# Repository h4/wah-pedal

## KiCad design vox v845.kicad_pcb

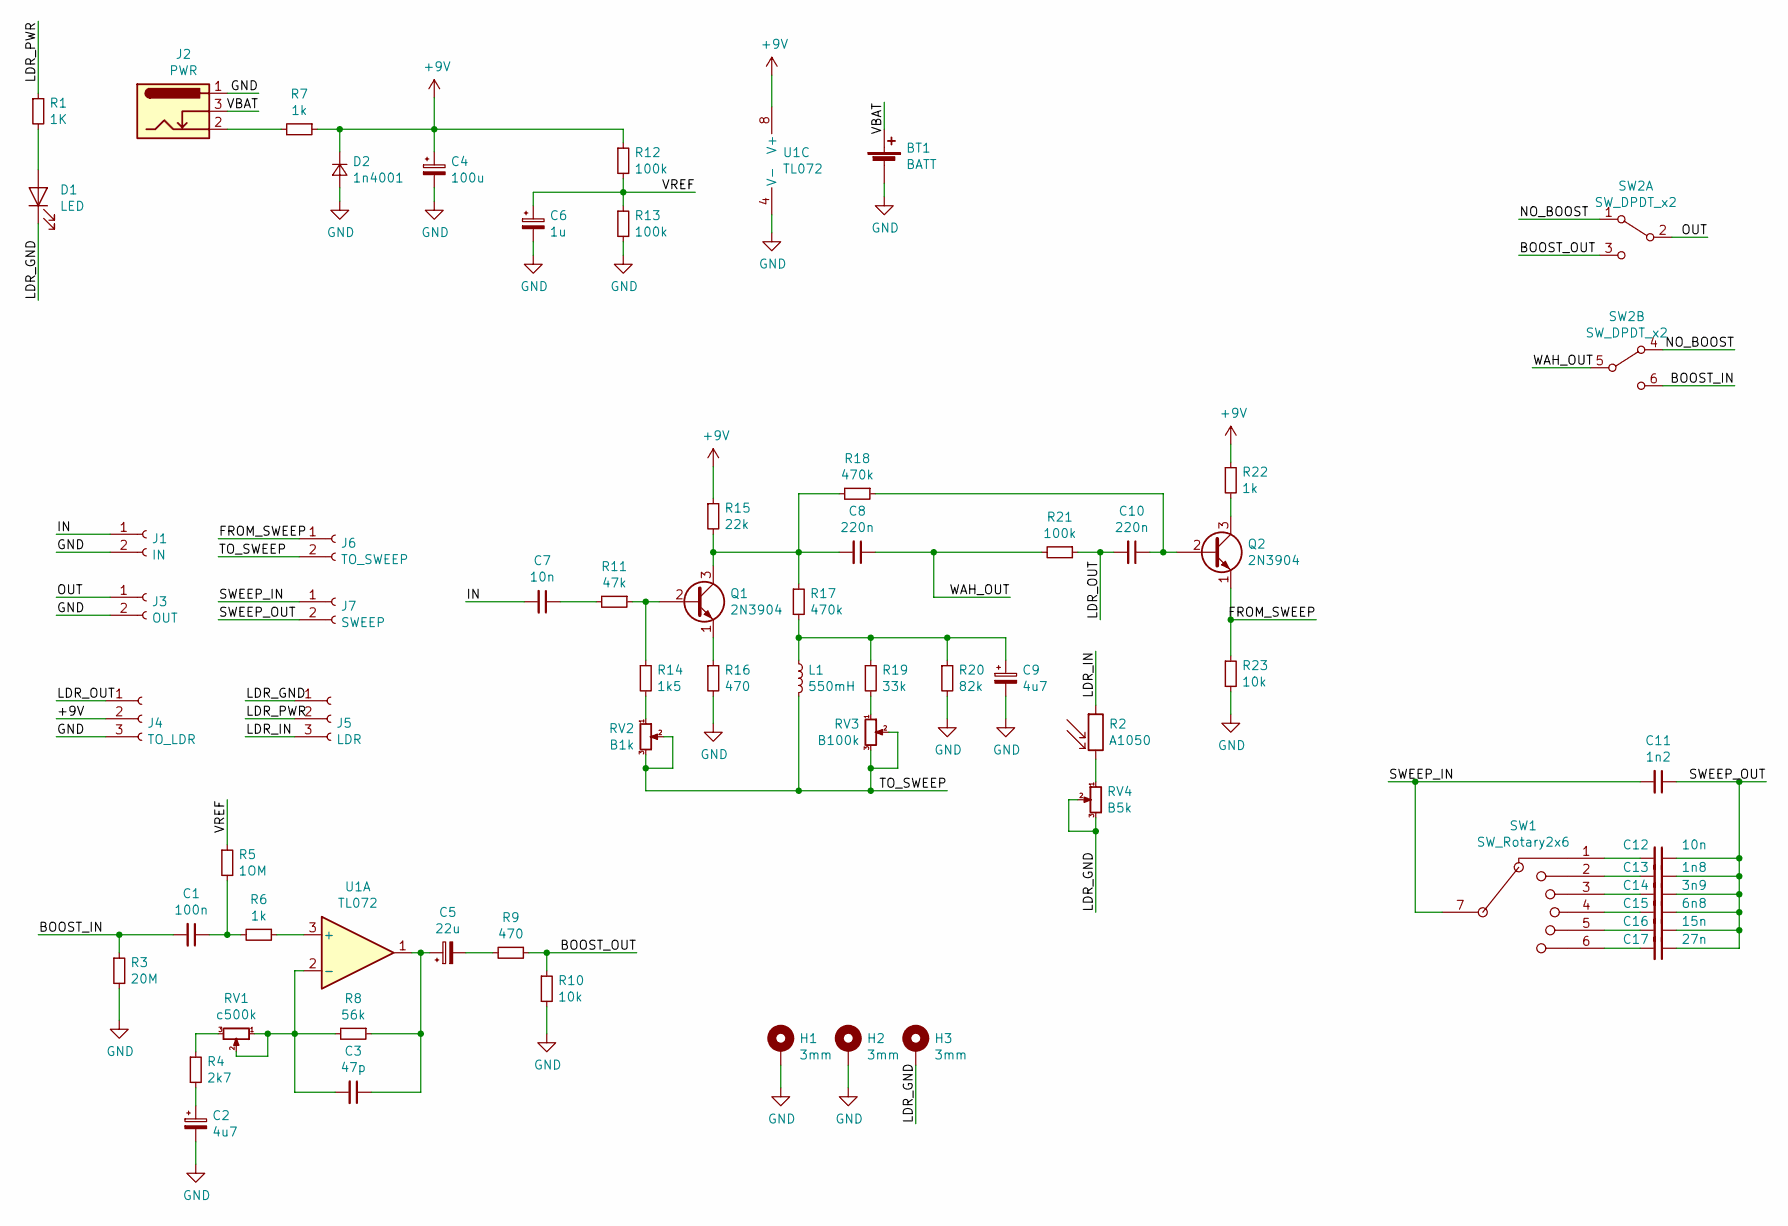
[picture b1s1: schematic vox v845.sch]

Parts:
BT1: BATT; JST_XH_B2B-XH-A_1x02_P2.50mm_Vertical
C1: 100n; C_Rect_L7.0mm_W3.5mm_P5.00mm
C2, C9: 4u7; CP_Radial_D5.0mm_P2.50mm
C3: 47p; C_Disc_D4.3mm_W1.9mm_P5.00mm
C4: 100u; CP_Radial_D8.0mm_P3.80mm
C5: 22u; CP_Radial_D5.0mm_P2.50mm
C6: 1u; CP_Radial_D5.0mm_P2.50mm
C7, C12: 10n; C_Rect_L7.0mm_W3.5mm_P5.00mm
C8, C10: 220n; C_Rect_L7.0mm_W3.5mm_P5.00mm
C11: 1n2; C_Rect_L7.0mm_W3.5mm_P5.00mm
C13: 1n8; C_Rect_L7.0mm_W3.5mm_P5.00mm
C14: 3n9; C_Rect_L7.0mm_W3.5mm_P5.00mm
C15: 6n8; C_Rect_L7.0mm_W3.5mm_P5.00mm
C16: 15n; C_Rect_L7.0mm_W3.5mm_P5.00mm
C17: 27n; C_Rect_L7.0mm_W3.5mm_P5.00mm
D1: LED; LED_D5.0mm_Horizontal_O1.27mm_Z3.0mm
D2: 1n4001; D_DO-15_P12.70mm_Horizontal
H1, H2, H3: 3mm; MountingHole_3.2mm_M3_Pad
J1: IN; JST_XH_B2B-XH-A_1x02_P2.50mm_Vertical
J2: PWR; JST_XH_B3B-XH-A_1x03_P2.50mm_Vertical
J3: OUT; JST_XH_B2B-XH-A_1x02_P2.50mm_Vertical
J4: TO_LDR; JST_XH_B3B-XH-A_1x03_P2.50mm_Vertical
J5: LDR; JST_XH_B3B-XH-A_1x03_P2.50mm_Vertical
J6: TO_SWEEP; JST_XH_B2B-XH-A_1x02_P2.50mm_Vertical
J7: SWEEP; JST_XH_B2B-XH-A_1x02_P2.50mm_Vertical
L1: 550mH; Inductor_VOX_L1A
Q1, Q2: 2N3904; TO-92_Inline_Wide
R1: 1K; R_Axial_DIN0204_L3.6mm_D1.6mm_P7.62mm_Horizontal
R2: A1050; R_LDR_D6.4mm_P3.4mm_Vertical
R3: 20M; R_Axial_DIN0411_L9.9mm_D3.6mm_P15.24mm_Horizontal
R4: 2k7; R_Axial_DIN0411_L9.9mm_D3.6mm_P15.24mm_Horizontal
R5: 1OM; R_Axial_DIN0411_L9.9mm_D3.6mm_P15.24mm_Horizontal
R6, R7, R22: 1k; R_Axial_DIN0411_L9.9mm_D3.6mm_P15.24mm_Horizontal
R8: 56k; R_Axial_DIN0411_L9.9mm_D3.6mm_P15.24mm_Horizontal
R9, R16: 470; R_Axial_DIN0411_L9.9mm_D3.6mm_P15.24mm_Horizontal
R10, R23: 10k; R_Axial_DIN0411_L9.9mm_D3.6mm_P15.24mm_Horizontal
R11: 47k; R_Axial_DIN0411_L9.9mm_D3.6mm_P15.24mm_Horizontal
R12, R13, R21: 100k; R_Axial_DIN0411_L9.9mm_D3.6mm_P15.24mm_Horizontal
R14: 1k5; R_Axial_DIN0411_L9.9mm_D3.6mm_P15.24mm_Horizontal
R15: 22k; R_Axial_DIN0411_L9.9mm_D3.6mm_P15.24mm_Horizontal
R17, R18: 470k; R_Axial_DIN0411_L9.9mm_D3.6mm_P15.24mm_Horizontal
R19: 33k; R_Axial_DIN0411_L9.9mm_D3.6mm_P15.24mm_Horizontal
R20: 82k; R_Axial_DIN0411_L9.9mm_D3.6mm_P15.24mm_Horizontal
RV1: c500k; JST_XH_B3B-XH-A_1x03_P2.50mm_Vertical
RV2: B1k; JST_XH_B3B-XH-A_1x03_P2.50mm_Vertical
RV3: B100k; JST_XH_B3B-XH-A_1x03_P2.50mm_Vertical
RV4: B5k; JST_XH_B3B-XH-A_1x03_P2.50mm_Vertical
SW1: SW_Rotary2x6; JST_XH_B7B-XH-A_1x07_P2.50mm_Vertical
SW2: SW_DPDT_x2; SW_PUSH_DPDT_Horizontal
U1: TL072; DIP-8_W7.62mm_Socket_LongPads

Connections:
+9V: C4.1, D2.1 (K), J4.2, R7.1, R12.1, R15.1, R22.1, U1.8 (V+)
/BOOST_IN: C1.2, R3.1, SW2.6 (C)
/BOOST_OUT: R9.1, R10.1, SW2.3 (C)
/FROM_SWEEP: J6.1, Q2.1 (E), R23.1
/IN: C7.2, J1.1
/LDR_GND: D1.1 (K), H3.1, J5.1, RV4.2, RV4.3
/LDR_IN: J5.3, R2.1
/LDR_OUT: C10.2, J4.1, R21.1
/LDR_PWR: J5.2, R1.1
/NO_BOOST: SW2.1 (A), SW2.4 (A)
/OUT: J3.1, SW2.2 (B)
/SWEEP_IN: C11.2, J7.1, SW1.7
/SWEEP_OUT: C11.1, C12.1, C13.1, C14.1, C15.1, C16.1, C17.1, J7.2
/TO_SWEEP: J6.2, L1.2, RV2.2, RV2.3, RV3.2, RV3.3
/VBAT: BT1.1 (+), J2.3
/VREF: C6.1, R5.1, R12.2, R13.1
/WAH_OUT: C8.1, R21.2, SW2.5 (B)
GND: BT1.2 (-), C2.2, C4.2, C6.2, C9.2, D2.2 (A), H1.1, H2.1, J1.2, J2.1, J3.2, J4.3, R3.2, R10.2, R13.2, R16.2, R20.2, R23.2, U1.4 (V-)
unnamed: C1.1, R5.2, R6.2
unnamed: C2.1, R4.2
unnamed: C3.1, C5.1, R8.1, U1.1
unnamed: C3.2, R8.2, RV1.1, RV1.2, U1.2 (-)
unnamed: C5.2, R9.2
unnamed: C7.1, R11.2
unnamed: C8.2, Q1.3 (C), R15.2, R17.1, R18.2
unnamed: C9.1, L1.1, R17.2, R19.1, R20.1
unnamed: C10.1, Q2.2 (B), R18.1
unnamed: C12.2, SW1.1
unnamed: C13.2, SW1.2
unnamed: C14.2, SW1.3
unnamed: C15.2, SW1.4
unnamed: C16.2, SW1.5
unnamed: C17.2, SW1.6
unnamed: D1.2 (A), R1.2
unnamed: J2.2, R7.2
unnamed: Q1.1 (E), R16.1
unnamed: Q1.2 (B), R11.1, R14.1
unnamed: Q2.3 (C), R22.2
unnamed: R2.2, RV4.1
unnamed: R4.1, RV1.3
unnamed: R6.1, U1.3 (+)
unnamed: R14.2, RV2.1
unnamed: R19.2, RV3.1

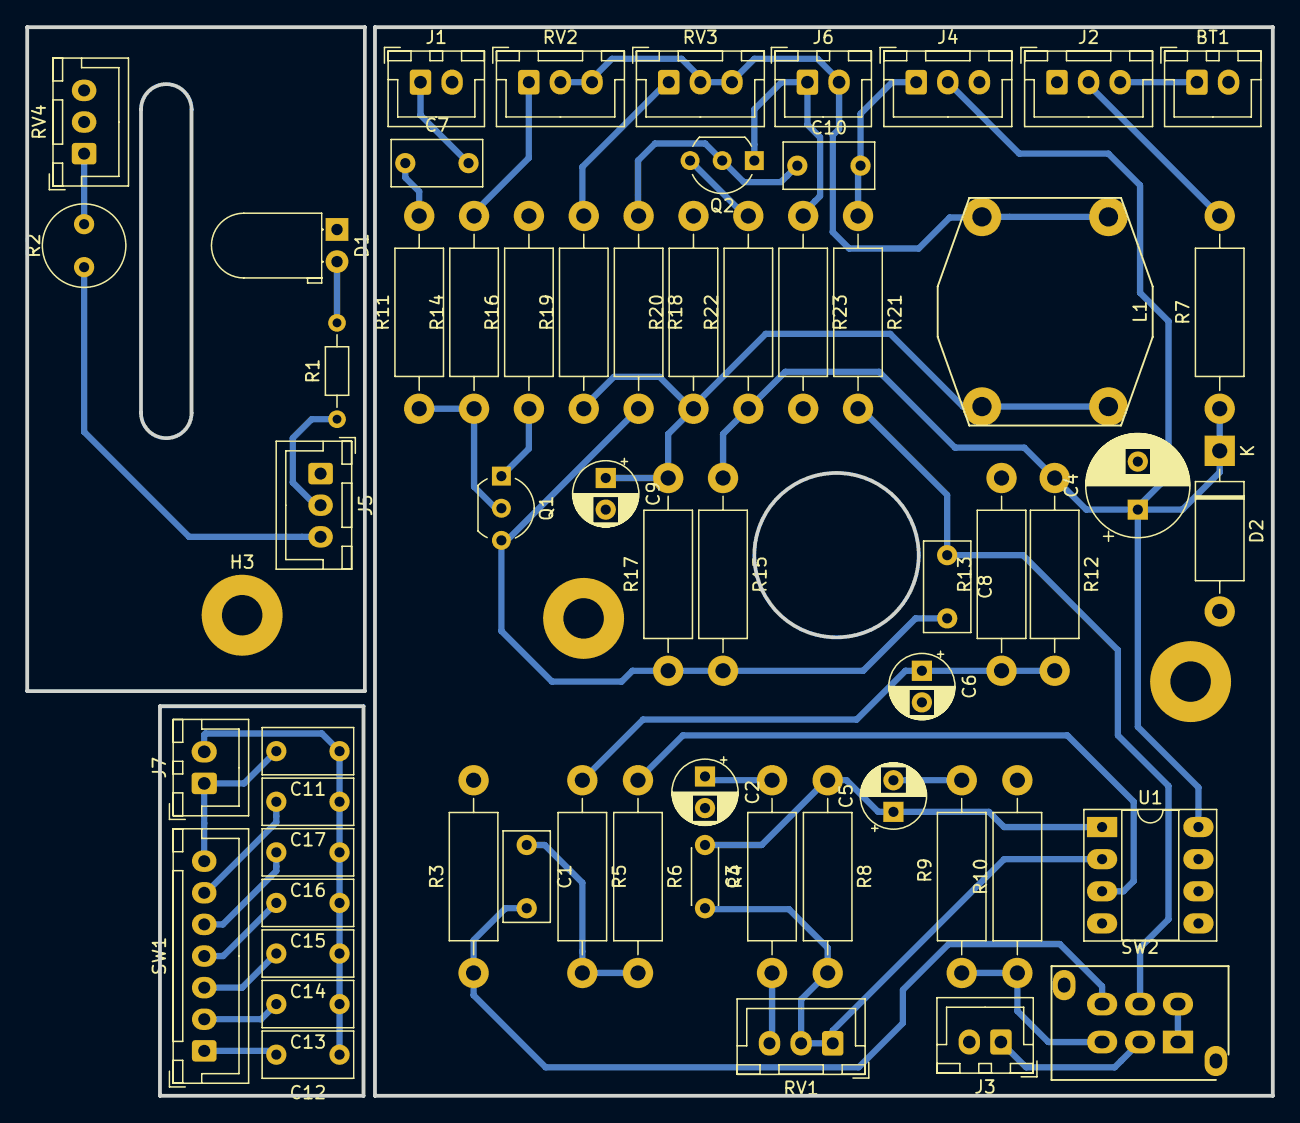
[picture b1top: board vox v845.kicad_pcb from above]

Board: 2 copper layers, 98.5 x 84.5 mm, 63 parts (0 on the bottom side), 43 nets.
